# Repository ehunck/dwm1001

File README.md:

# DWM1001

The purpose of this project is to get the DWM1001 module up and running.

So far, a simple breakout board has been made for the module and the files for that are available here.

Any code written for bringing the devices up will also detailed here.  The initial intent is to use the preloaded firmware on the module and to conduct simple ranging.

More to come!

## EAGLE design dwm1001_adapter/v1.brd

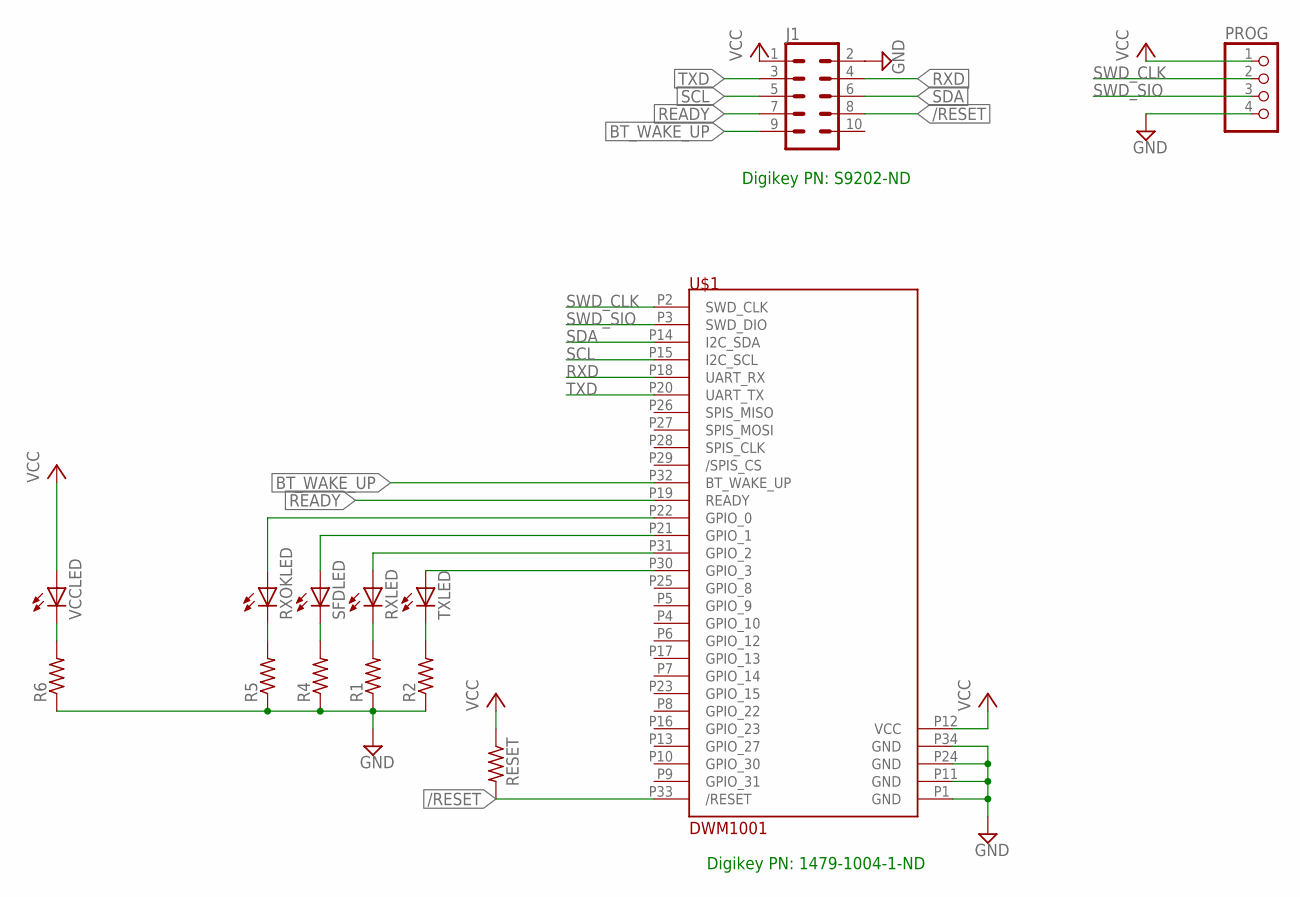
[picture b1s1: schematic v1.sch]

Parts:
J1: CONN_05X2RAF; 2X5-RAF
PROG: PINHD-1X4; 1X04
R1, R2, R4, R5, R6: R-US_R0603; R0603
RESET: R-US_R0603; R0603
RXLED: LEDCHIPLED_0603; CHIPLED_0603
RXOKLED: LEDCHIPLED_0603; CHIPLED_0603
SFDLED: LEDCHIPLED_0603; CHIPLED_0603
TXLED: LEDCHIPLED_0603; CHIPLED_0603
U$1: DWM1001; DWM1001_LAND_PATTERN
VCCLED: LEDCHIPLED_0603; CHIPLED_0603

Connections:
/RESET: J1.8, RESET.2, U$1.P33 (/RESET)
BT_WAKE_UP: J1.9, U$1.P32 (BT_WAKE_UP)
GND: J1.2, PROG.4, R1.1, R2.1, R4.1, R5.1, R6.1, U$1.P1 (GND), U$1.P11 (GND), U$1.P24 (GND), U$1.P34 (GND)
unnamed: R1.2, RXLED.C
unnamed: R2.2, TXLED.C
unnamed: TXLED.A, U$1.P30 (GPIO_3)
unnamed: RXLED.A, U$1.P31 (GPIO_2)
unnamed: R4.2, SFDLED.C
unnamed: R5.2, RXOKLED.C
unnamed: SFDLED.A, U$1.P21 (GPIO_1)
unnamed: RXOKLED.A, U$1.P22 (GPIO_0)
unnamed: R6.2, VCCLED.C
READY: J1.7, U$1.P19 (READY)
RXD: J1.4, U$1.P18 (UART_RX)
SCL: J1.5, U$1.P15 (I2C_SCL)
SDA: J1.6, U$1.P14 (I2C_SDA)
SWD_CLK: PROG.2, U$1.P2 (SWD_CLK)
SWD_SIO: PROG.3, U$1.P3 (SWD_DIO)
TXD: J1.3, U$1.P20 (UART_TX)
VCC: J1.1, PROG.1, RESET.1, U$1.P12 (VCC), VCCLED.A

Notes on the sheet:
Digikey PN: S9202-ND
Digikey PN: 1479-1004-1-ND

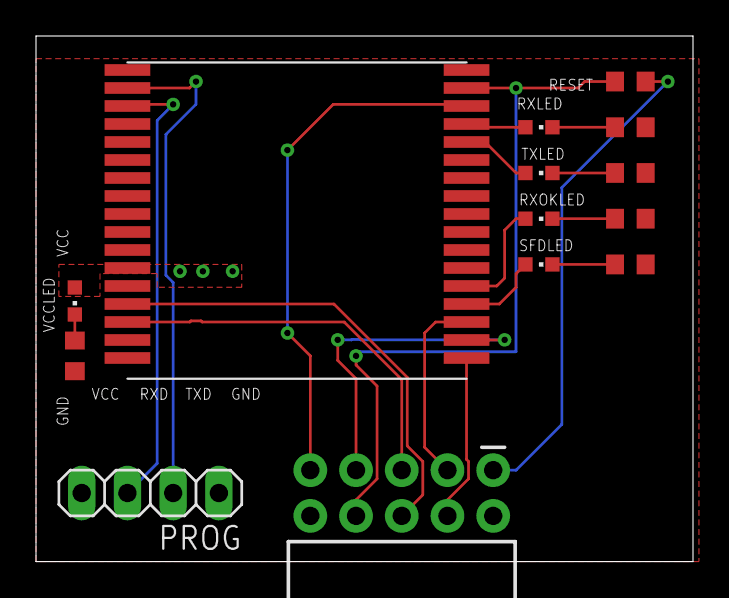
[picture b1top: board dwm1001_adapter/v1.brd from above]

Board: 2 copper layers, 36.5 x 29.2 mm, 14 parts (0 on the bottom side), 20 nets.

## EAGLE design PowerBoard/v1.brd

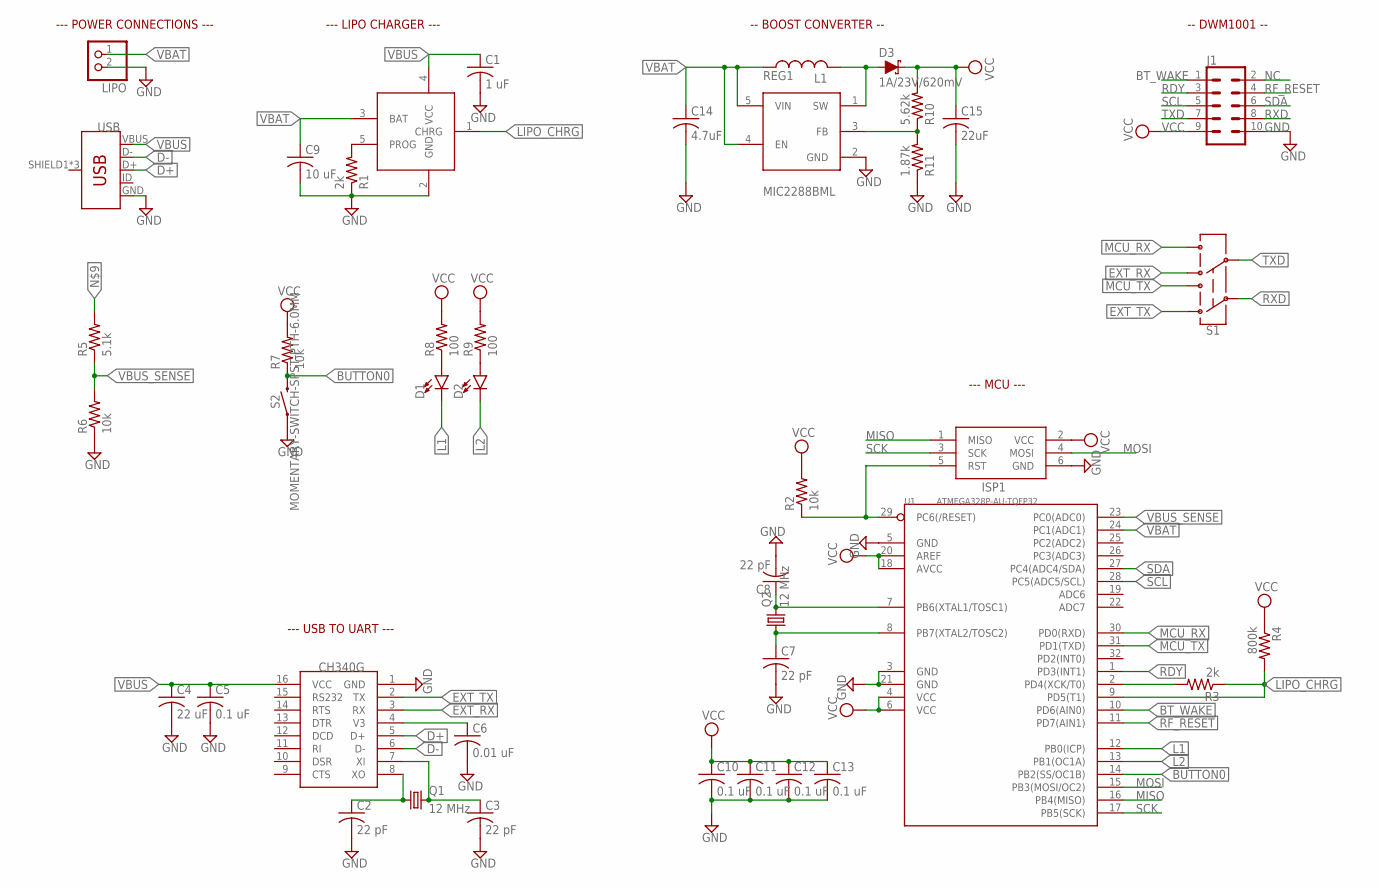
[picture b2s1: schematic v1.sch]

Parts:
C1: 1 uF; C0603
C2, C3, C7, C8: 22 pF; C0603
C4: 22 uF; C0603
C5, C10, C11, C12, C13: 0.1 uF; C0603
C6: 0.01 uF; C0603
C9: 10 uF; C0603
C14: 4.7uF; C0603
C15: 22uF; C0603
D1, D2: LED0603; LED-0603
D3: 1A/23V/620mV; SOD-323
ISP1: AVRISP-BOX
J1: CONN_05X2SHD; 2X5-SHROUDED
L1: L-USL4532P; L4532P
LIPO: JST_2PIN-THM; JST-PH-2-THM
Q1, Q2: 12 MHz; SM49
R1, R3: 2k; R0603
R2, R6, R7: 10k; R0603
R4: 800k; R0603
R5: 5.1k; R0603
R8, R9: 100; R0603
R10: 5.62k; R0603
R11: 1.87k; R0603
REG1: MIC2288BML; SOT23-5L
S1: SWITCH-DPDT-SMD-AYZ0202; SWITCH_DPDT_SMD_AYZ0202
S2: MOMENTARY-SWITCH-SPST-PTH-6.0MM; TACTILE_SWITCH_PTH_6.0MM
U1: ATMEGA328P-AU-TQFP32; TQFP32-0.8-7X7MM
U$1: LTC4054
U$2: CH340G; SOIC16
USB: USB_MICRO-B_FEMALE-SMT; USB-B-MICRO-SMD

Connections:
BT_WAKE: J1.1, U1.10 (PD6(AIN0))
BUTTON0: R7.1, S2.3 (2), U1.14 (PB2(SS/OC1B))
D+: U$2.5 (D+), USB.D+
D-: U$2.6 (D-), USB.D-
EXT_RX: S1.4, U$2.3 (RX)
EXT_TX: S1.1, U$2.2 (TX)
GND: C1.2, C2.2, C3.2, C4.2, C5.2, C6.2, C7.2, C8.2, C9.2, C10.2, C11.2, C12.2, C13.2, C14.2, C15.2, ISP1.6 (GND), J1.10, LIPO.2 (1), R1.1, R6.1, R11.1, REG1.2 (GND), S2.1, U1.3 (GND), U1.5 (GND), U1.21 (GND), U$1.2 (GND), U$2.1 (GND), USB.GND
L1: D1.C, U1.12 (PB0(ICP))
L2: D2.C, U1.13 (PB1(OC1A))
LIPO_CHRG: R3.1, R4.2, U1.9 (PD5(T1)), U$1.1 (CHRG)
MCU_RX: S1.6, U1.30 (PD0(RXD))
MCU_TX: S1.3, U1.31 (PD1(TXD))
MISO: ISP1.1 (MISO), U1.16 (PB4(MISO))
MOSI: ISP1.4 (MOSI), U1.15 (PB3(MOSI/OC2))
unnamed: R1.2, U$1.5 (PROG)
unnamed: R3.2, U1.2 (PD4(XCK/T0))
unnamed: C6.1, U$2.4 (V3)
unnamed: C8.1, Q2.2, U1.7 (PB6(XTAL1/TOSC1))
unnamed: C3.1, Q1.2, U$2.7 (XI)
unnamed: C2.1, Q1.1, U$2.8 (XO)
unnamed: ISP1.5 (RST), R2.1, U1.29 (PC6(/RESET))
unnamed: C7.1, Q2.1, U1.8 (PB7(XTAL2/TOSC2))
unnamed: D1.A, R8.1
unnamed: D2.A, R9.1
unnamed: D3.A, L1.2, REG1.1 (SW)
unnamed: R10.1, R11.2, REG1.3 (FB)
NC: J1.2
RDY: J1.3, U1.1 (PD3(INT1))
RF_RESET: J1.4, U1.11 (PD7(AIN1))
RXD: J1.8, S1.2
SCK: ISP1.3 (SCK), U1.17 (PB5(SCK))
SCL: J1.5, U1.28 (PC5(ADC5/SCL))
SDA: J1.6, U1.27 (PC4(ADC4/SDA))
TXD: J1.7, S1.5
VBAT: C9.1, C14.1, L1.1, LIPO.1 (2), REG1.4 (EN), REG1.5 (VIN), U1.24 (PC1(ADC1)), U$1.3 (BAT)
VBUS: C1.1, C4.1, C5.1, U$1.4 (VCC), U$2.16 (VCC), USB.VBUS
VBUS_SENSE: R5.1, R6.2, U1.23 (PC0(ADC0))
VCC: C10.1, C11.1, C12.1, C13.1, C15.1, D3.C, ISP1.2 (VCC), J1.9, R2.2, R4.1, R7.2, R8.2, R9.2, R10.2, U1.4 (VCC), U1.6 (VCC), U1.18 (AVCC), U1.20 (AREF)

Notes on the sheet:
--- LIPO CHARGER ---
--- POWER CONNECTIONS ---
--- USB TO UART ---
--- MCU ---
-- BOOST CONVERTER --
-- DWM1001 --

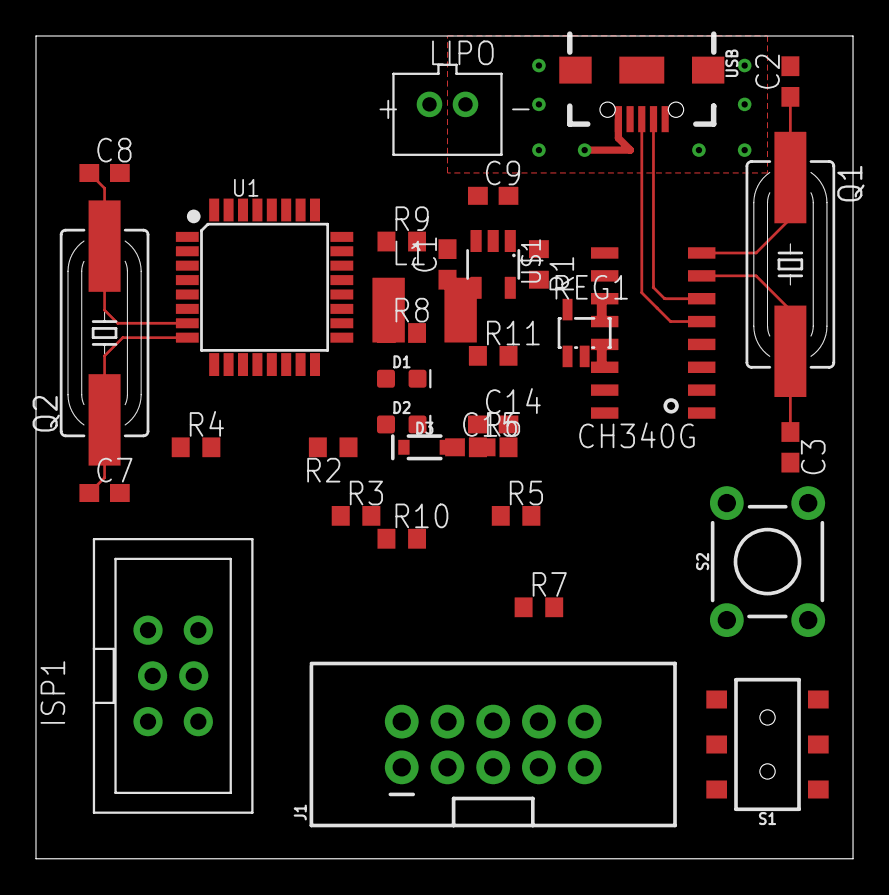
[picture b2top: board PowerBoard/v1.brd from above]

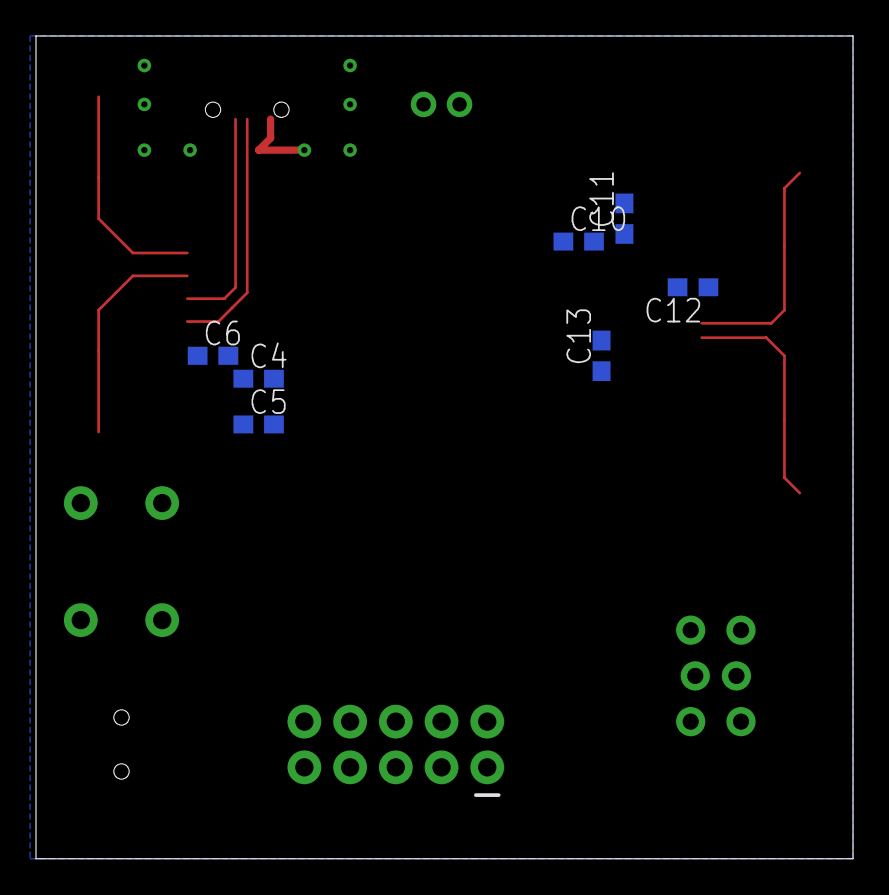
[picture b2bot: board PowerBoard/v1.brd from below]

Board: 2 copper layers, 45.4 x 45.7 mm, 42 parts (7 on the bottom side), 37 nets.

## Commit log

2018-03-07 -commit the hardware files for the dwm1001 adapter
2018-03-07 -added git ignore
2018-03-19 -updates to schematic and board
2018-03-19 Create LICENSE
2018-03-29 -updated README -added schematic and board pictures
2018-03-29 -initial commit of arduino code for driving the dwm1001 module
2018-03-29 (WIP) - updated files to compile
2018-07-06 -removed reset switch and changed reset resistor to pull up
2019-11-26 - updated board and schematic

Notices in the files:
parts and their libraries:
SparkFun-Connectors: Licensing: Creative Commons ShareAlike 4.0 International - https://creativecommons.org/licenses/by-sa/4.0
